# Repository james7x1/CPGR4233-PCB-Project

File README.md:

# CPGR4233-PCB-Project
Voltmeter PCB design project for LeTourneau University CPGR4233.

Derived from 20+ years of PCB designs created by Intro to Microcomputer Design TAs.
Recent Contributors:

Rev 5 - Samuel Johnson, Allen Morrison, Joshua Allen (AJ)

Rev 4 - Samuel Johnson

Rev 3 - Jackson Miller

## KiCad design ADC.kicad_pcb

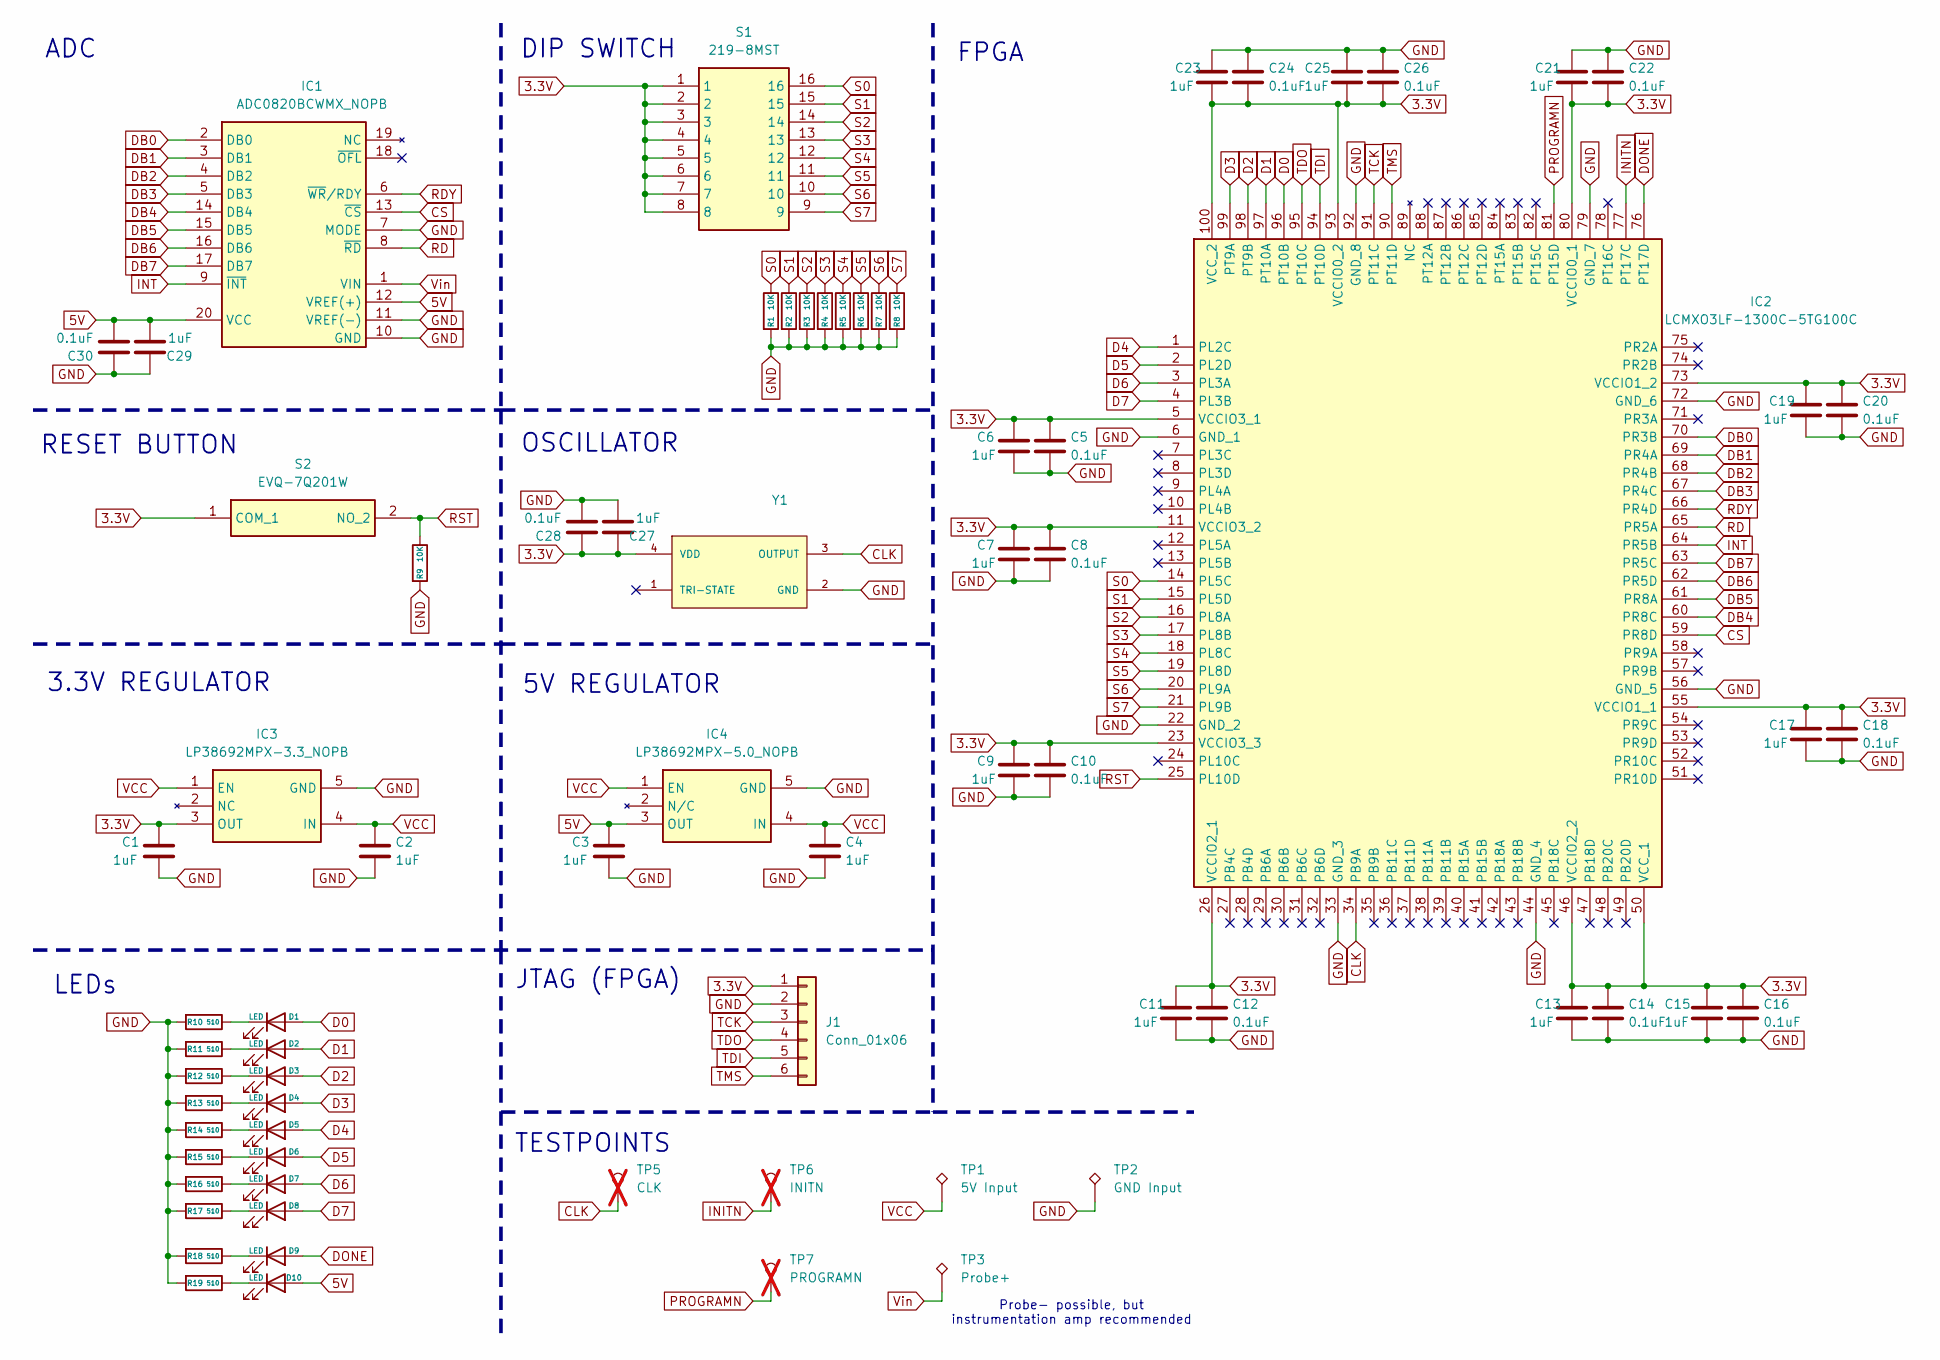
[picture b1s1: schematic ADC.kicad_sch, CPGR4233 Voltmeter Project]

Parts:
C1, C2, C3, C4, C6, C7, C9, C11, C13, C15, C17, C19, C21, C23, C25, C27, C29: 1uF; C_0805_2012Metric_Pad1.18x1.45mm_HandSolder; Manufacturer_Part_Number GRM21BR71A105MA01L
C5, C8, C10, C12, C14, C16, C18, C20, C22, C24, C26, C28, C30: 0.1uF; C_0805_2012Metric_Pad1.18x1.45mm_HandSolder; Manufacturer_Part_Number GJ4216C81E104JA01D
D1, D2, D3, D4, D5, D6, D7, D8, D9, D10: LED; LED_0805_2012Metric_Pad1.15x1.40mm_HandSolder; Manufacturer_Part_Number 150080GS75000
IC1: ADC0820BCWMX_NOPB; SOIC-20W_7.5x12.8mm_P1.27mm; Mouser Part Number 926-ADC0820BCWMXNOPB
IC2: LCMXO3LF-1300C-5TG100C; TQFP-100_14x14mm_P0.5mm; Mouser Part Number 842-O3LF1300C5TG100C
IC3: LP38692MPX-3.3_NOPB; SOT-223-5; Mouser Part Number 926-LP38692MPX33NOPB
IC4: LP38692MPX-5.0_NOPB; SOT-223-5; Mouser Part Number 926-LP38692MPX50NOPB
J1: Conn_01x06; PinHeader_1x06_P2.54mm_Vertical; Manufacturer_Part_Number G800W302018EU
R1, R2, R3, R4, R5, R6, R7, R8, R9: 10K; R_0805_2012Metric_Pad1.20x1.40mm_HandSolder; Manufacturer_Part_Number AC0805FR-7W10KL
R10, R11, R12, R13, R14, R15, R16, R17, R18, R19: 510; R_0805_2012Metric_Pad1.20x1.40mm_HandSolder; Manufacturer_Part_Number ERJ-PB6D5100V
S1: 219-8MST; SW_DIP_SPSTx08_Slide_6.7x21.88mm_W8.61mm_P2.54mm_LowProfile; Mouser Part Number 774-2198MST
S2: EVQ-7Q201W; SW_SPST_EVQQ2; Mouser Part Number 667-EVQ-7Q201W
TP1: 5V Input; TestPoint_THTPad_2.5x2.5mm_Drill1.2mm; Manufacturer_Part_Number 4952
TP2: GND Input; TestPoint_THTPad_2.5x2.5mm_Drill1.2mm; Manufacturer_Part_Number 4952
TP3: Probe+; TestPoint_THTPad_2.5x2.5mm_Drill1.2mm; Manufacturer_Part_Number 4952
TP5: CLK; TestPoint_Pad_1.5x1.5mm; not fitted
TP6: INITN; TestPoint_Pad_1.5x1.5mm; not fitted
TP7: PROGRAMN; TestPoint_Pad_1.5x1.5mm; not fitted
Y1: CDFN-4_3.2x5mm_P2.54mm; Manufacturer_Part_Number ECS-5032MV-320-BN-TR

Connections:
5V: C3.1, C29.2, C30.2, D10.2 (A), IC1.12 (VREF(+)), IC1.20 (VCC), IC4.3 (OUT)
CLK: IC2.34 (PB9A), TP5.1 (1_1), Y1.3 (OUTPUT)
CS: IC1.13 (~CS), IC2.59 (PR8D)
D0: D1.2 (A), IC2.96 (PT10B)
D1: D2.2 (A), IC2.97 (PT10A)
D2: D3.2 (A), IC2.98 (PT9B)
D3: D4.2 (A), IC2.99 (PT9A)
D4: D5.2 (A), IC2.1 (PL2C)
D5: D6.2 (A), IC2.2 (PL2D)
D6: D7.2 (A), IC2.3 (PL3A)
D7: D8.2 (A), IC2.4 (PL3B)
DB0: IC1.2 (DB0), IC2.70 (PR3B)
DB1: IC1.3 (DB1), IC2.69 (PR4A)
DB2: IC1.4 (DB2), IC2.68 (PR4B)
DB3: IC1.5 (DB3), IC2.67 (PR4C)
DB4: IC1.14 (DB4), IC2.60 (PR8C)
DB5: IC1.15 (DB5), IC2.61 (PR8A)
DB6: IC1.16 (DB6), IC2.62 (PR5D)
DB7: IC1.17 (DB7), IC2.63 (PR5C)
DONE: D9.2 (A), IC2.76 (PT17D)
GND: C1.2, C2.2, C3.2, C4.2, C5.2, C6.2, C7.2, C8.2, C9.2, C10.2, C11.2, C12.2, C13.2, C14.2, C15.2, C16.2, C17.2, C18.2, C19.2, C20.2, C21.1, C22.1, C23.1, C24.1, C25.1, C26.1, C27.2, C28.2, C29.1, C30.1, IC1.7 (MODE), IC1.10 (GND), IC1.11 (VREF(-)), IC2.6 (GND_1), IC2.22 (GND_2), IC2.33 (GND_3), IC2.44 (GND_4), IC2.56 (GND_5), IC2.72 (GND_6), IC2.79 (GND_7), IC2.92 (GND_8), IC3.5 (GND), IC4.5 (GND), J1.2, R1.2, R2.2, R3.2, R4.2, R5.2, R6.2, R7.2, R8.2, R9.2, R10.2, R11.2, R12.2, R13.2, R14.2, R15.2, R16.2, R17.2, R18.2, R19.2, TP2.1 (1_1), Y1.2 (GND)
INITN: IC2.77 (PT17C), TP6.1 (1_1)
INT: IC1.9 (~INT), IC2.64 (PR5B)
unnamed: D1.1 (K), R10.1
unnamed: D2.1 (K), R11.1
unnamed: D3.1 (K), R12.1
unnamed: D4.1 (K), R13.1
unnamed: D5.1 (K), R14.1
unnamed: D6.1 (K), R15.1
unnamed: D7.1 (K), R16.1
unnamed: D8.1 (K), R17.1
unnamed: D9.1 (K), R18.1
unnamed: D10.1 (K), R19.1
PROGRAMN: IC2.81 (PT15D), TP7.1 (1_1)
RD: IC1.8 (~RD), IC2.65 (PR5A)
RDY: IC1.6 (~WR/RDY), IC2.66 (PR4D)
S0: IC2.14 (PL5C), R1.1, S1.16
S1: IC2.15 (PL5D), R2.1, S1.15
S2: IC2.16 (PL8A), R3.1, S1.14
S3: IC2.17 (PL8B), R4.1, S1.13
S4: IC2.18 (PL8C), R5.1, S1.12
S5: IC2.19 (PL8D), R6.1, S1.11
S6: IC2.20 (PL9A), R7.1, S1.10
S7: IC2.21 (PL9B), R8.1, S1.9
TCK: IC2.91 (PT11C), J1.3
TDI: IC2.94 (PT10D), J1.5
TDO: IC2.95 (PT10C), J1.4
TMS: IC2.90 (PT11D), J1.6
VCC: C2.1, C4.1, IC3.1 (EN), IC3.4 (IN), IC4.1 (EN), IC4.4 (IN), TP1.1 (1_1)
Vin: IC1.1 (VIN), TP3.1 (1_1)

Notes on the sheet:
LEDs
DIP SWITCH
3.3V REGULATOR
Probe- possible, but instrumentation amp recommended
RESET BUTTON
5V REGULATOR
JTAG (FPGA)
OSCILLATOR
ADC
FPGA
TESTPOINTS

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
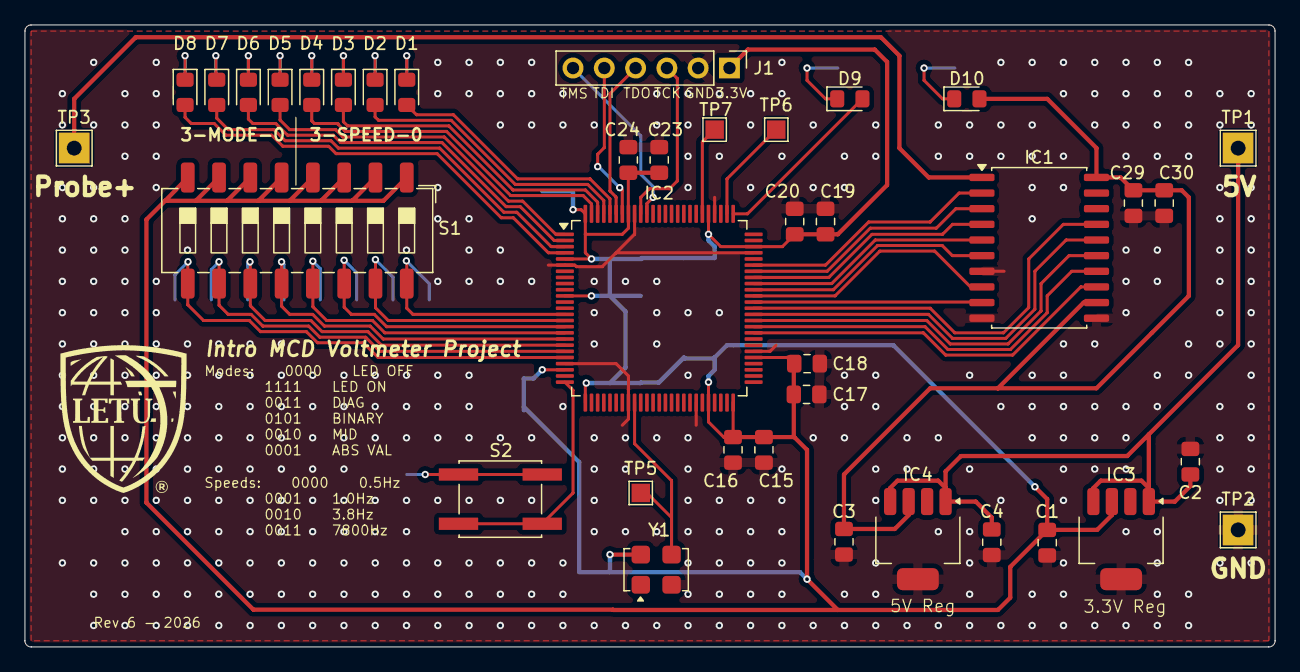
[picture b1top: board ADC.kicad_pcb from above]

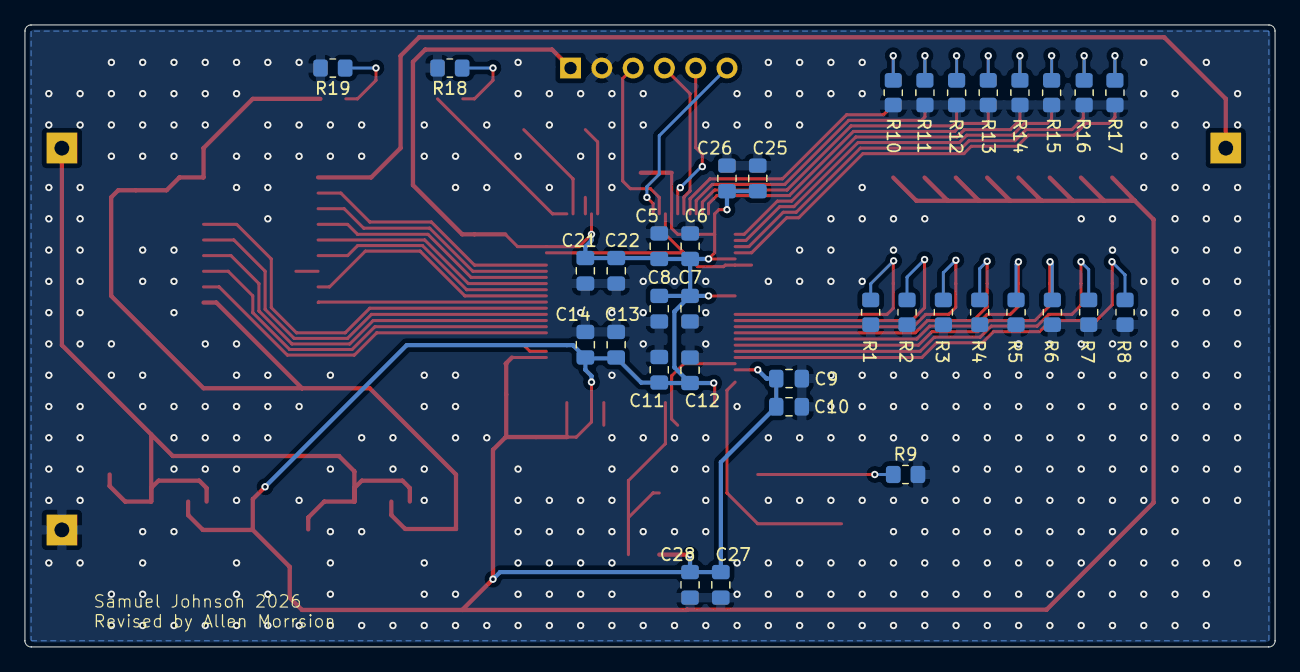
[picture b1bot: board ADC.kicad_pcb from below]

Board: 2 copper layers, 101.5 x 50.5 mm, 73 parts (35 on the bottom side), 53 nets.

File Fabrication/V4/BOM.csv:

#,Manufacturer_Part_Number,Manufacturer_Name,Qty,Value,DNP,Reference
1,GRM21BR71A105MA01L,Murata,17,1uF,,"C1,C2,C3,C4,C6,C7,C9,C11,C13,C15,C17,C19,C21,C23,C25,C27,C29"
2,GJ4216C81E104JA01D,Murata,13,0.1uF,,"C5,C8,C10,C12,C14,C16,C18,C20,C22,C24,C26,C28,C30"
3,150080GS75000,Würth Elektronik,10,LED,,"D1,D2,D3,D4,D5,D6,D7,D8,D9,D10"
4,ADC0820BCWMX/NOPB,Texas Instruments,1,,,IC1
5, LCMXO3LF-1300C-5TG100C ,Lattice Semiconductor,1,,,IC2
6,LP38692MPX-3.3/NOPB,Texas Instruments,1,,,IC3
7,LP38692MPX-5.0/NOPB,Texas Instruments,1,,,IC4
8,G800W302018EU,Amphenol ICC,1,,,J1
9,AC0805FR-7W10KL,YAGEO,9,10K,,"R1,R2,R3,R4,R5,R6,R7,R8,R9"
10,ERJ-PB6D5100V,Panasonic,10,510,,"R10,R11,R12,R13,R14,R15,R16,R17,R18,R19"
11,219-8MST,CTS,1,,,S1
12,EVQ-7Q201W,Panasonic,1,,,S2
13,4952,Keystone Electronics,4,"5V Input,GND Input,Probe+,Probe-",,"TP1,TP2,TP3,TP4"
14,,,3,"CLK,INITN,PROGRAMN",DNP,"TP5,TP6,TP7"
15,ECS-5032MV-320-BN-TR,ECS,1,,,Y1
